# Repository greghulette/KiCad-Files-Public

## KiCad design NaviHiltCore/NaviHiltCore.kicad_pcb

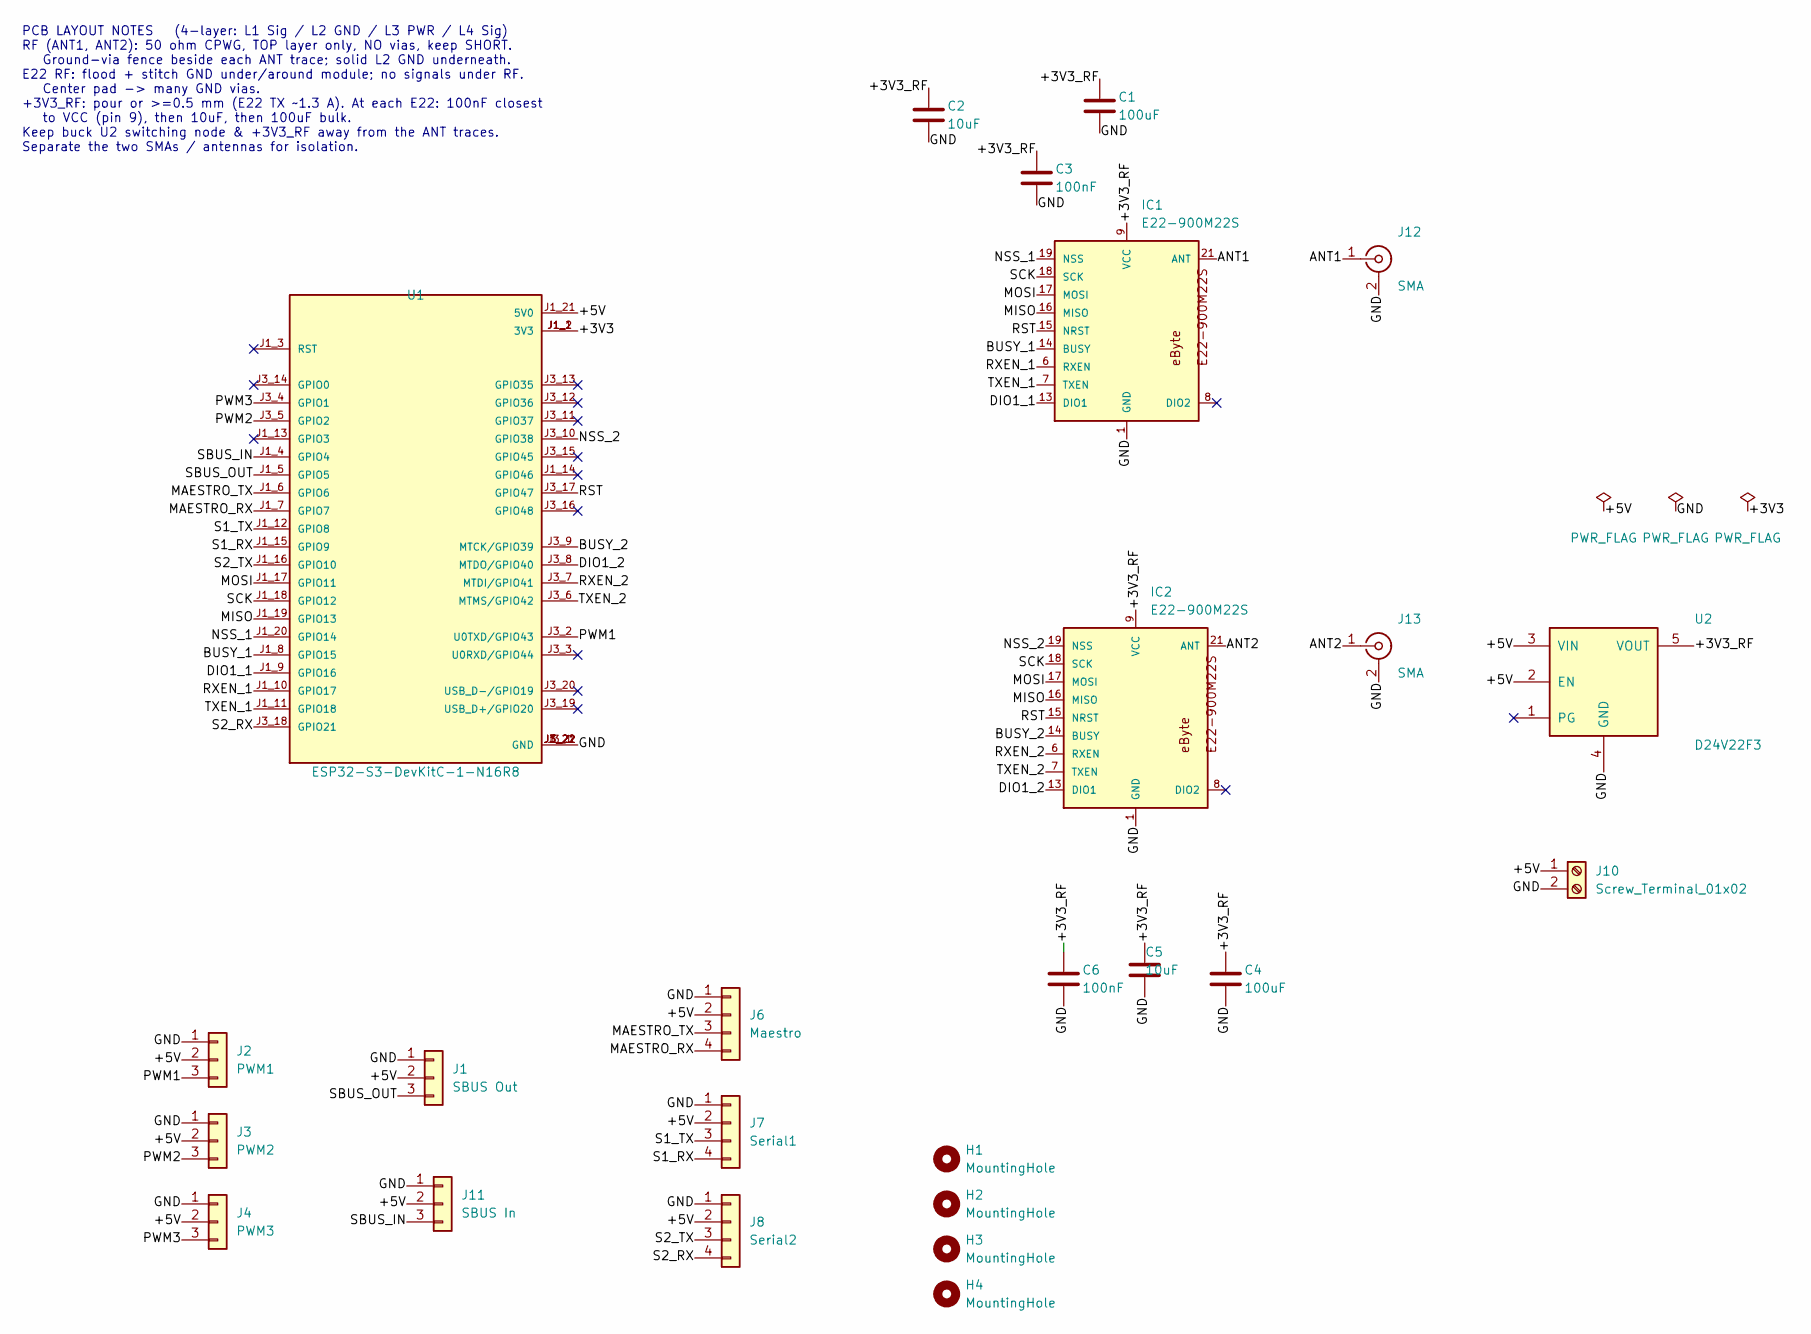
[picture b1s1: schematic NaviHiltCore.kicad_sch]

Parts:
C1, C4: 100uF; C_0805_2012Metric
C2, C5: 10uF; C_0805_2012Metric
C3, C6: 100nF; C_0805_2012Metric
H1, H2, H3, H4: MountingHole; MountingHole_3.2mm_M3
IC1, IC2: E22-900M22S
J1: SBUS Out; PinHeader_1x03_P2.54mm_Vertical
J2: PWM1; PinHeader_1x03_P2.54mm_Vertical
J3: PWM2; PinHeader_1x03_P2.54mm_Vertical
J4: PWM3; PinHeader_1x03_P2.54mm_Vertical
J6: Maestro; PinHeader_1x04_P2.54mm_Vertical
J7: Serial1; PinHeader_1x04_P2.54mm_Vertical
J8: Serial2; PinHeader_1x04_P2.54mm_Vertical
J10: Screw_Terminal_01x02; TerminalBlock_CUI_TB007-508-02_1x02_P5.08mm_Horizontal
J11: SBUS In; PinHeader_1x03_P2.54mm_Vertical
J12, J13: SMA; SMA_Amphenol_132134_Vertical
U1: ESP32-S3-DevKitC-1-N16R8; ESP32-S3DevKit-Multi
U2: D24V22F3

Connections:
/+3V3: U1.J1_1 (3V3), U1.J1_2 (3V3)
/+3V3_RF: C1.1, C2.1, C3.1, C4.1, C5.1, C6.1, IC1.9 (VCC), IC2.9 (VCC), U2.5 (VOUT)
/+5V: J1.2, J2.2, J3.2, J4.2, J6.2, J7.2, J8.2, J10.1, J11.2, U1.J1_21 (5V0), U2.2 (EN), U2.3 (VIN)
/ANT1: IC1.21 (ANT), J12.1 (In)
/ANT2: IC2.21 (ANT), J13.1 (In)
/BUSY_1: IC1.14 (BUSY), U1.J1_8 (GPIO15)
/BUSY_2: IC2.14 (BUSY), U1.J3_9 (MTCK/GPIO39)
/DIO1_1: IC1.13 (DIO1), U1.J1_9 (GPIO16)
/DIO1_2: IC2.13 (DIO1), U1.J3_8 (MTDO/GPIO40)
/MAESTRO_RX: J6.4, U1.J1_7 (GPIO7)
/MAESTRO_TX: J6.3, U1.J1_6 (GPIO6)
/MISO: IC1.16 (MISO), IC2.16 (MISO), U1.J1_19 (GPIO13)
/MOSI: IC1.17 (MOSI), IC2.17 (MOSI), U1.J1_17 (GPIO11)
/NSS_1: IC1.19 (NSS), U1.J1_20 (GPIO14)
/NSS_2: IC2.19 (NSS), U1.J3_10 (GPIO38)
/PWM1: J2.3, U1.J3_2 (U0TXD/GPIO43)
/PWM2: J3.3, U1.J3_5 (GPIO2)
/PWM3: J4.3, U1.J3_4 (GPIO1)
/RST: IC1.15 (NRST), IC2.15 (NRST), U1.J3_17 (GPIO47)
/RXEN_1: IC1.6 (RXEN), U1.J1_10 (GPIO17)
/RXEN_2: IC2.6 (RXEN), U1.J3_7 (MTDI/GPIO41)
/S1_RX: J7.4, U1.J1_15 (GPIO9)
/S1_TX: J7.3, U1.J1_12 (GPIO8)
/S2_RX: J8.4, U1.J3_18 (GPIO21)
/S2_TX: J8.3, U1.J1_16 (GPIO10)
/SBUS_IN: J11.3, U1.J1_4 (GPIO4)
/SBUS_OUT: J1.3, U1.J1_5 (GPIO5)
/SCK: IC1.18 (SCK), IC2.18 (SCK), U1.J1_18 (GPIO12)
/TXEN_1: IC1.7 (TXEN), U1.J1_11 (GPIO18)
/TXEN_2: IC2.7 (TXEN), U1.J3_6 (MTMS/GPIO42)
GND: C1.2, C2.2, C3.2, C4.2, C5.2, C6.2, IC1.1 (GND), IC1.2 (GND), IC1.3 (GND), IC1.4 (GND), IC1.5 (GND), IC1.10 (GND), IC1.11 (GND), IC1.12 (GND), IC1.20 (GND), IC1.22 (GND), IC2.1 (GND), IC2.2 (GND), IC2.3 (GND), IC2.4 (GND), IC2.5 (GND), IC2.10 (GND), IC2.11 (GND), IC2.12 (GND), IC2.20 (GND), IC2.22 (GND), J1.1, J2.1, J3.1, J4.1, J6.1, J7.1, J8.1, J10.2, J11.1, J12.2 (Ext), J13.2 (Ext), U1.J1_22 (GND), U1.J3_1 (GND), U1.J3_21 (GND), U1.J3_22 (GND), U2.4 (GND)

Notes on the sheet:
PCB LAYOUT NOTES (4-layer: L1 Sig / L2 GND / L3 PWR / L4 Sig) RF (ANT1, ANT2): 50 ohm CPWG, TOP layer only, NO vias, keep SHORT. Ground-via fence beside each ANT trace; solid L2 GND underneath. E22 RF: flood + stitch GND under/around module; no signals under RF. Center pad -> many GND vias. +3V3_RF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

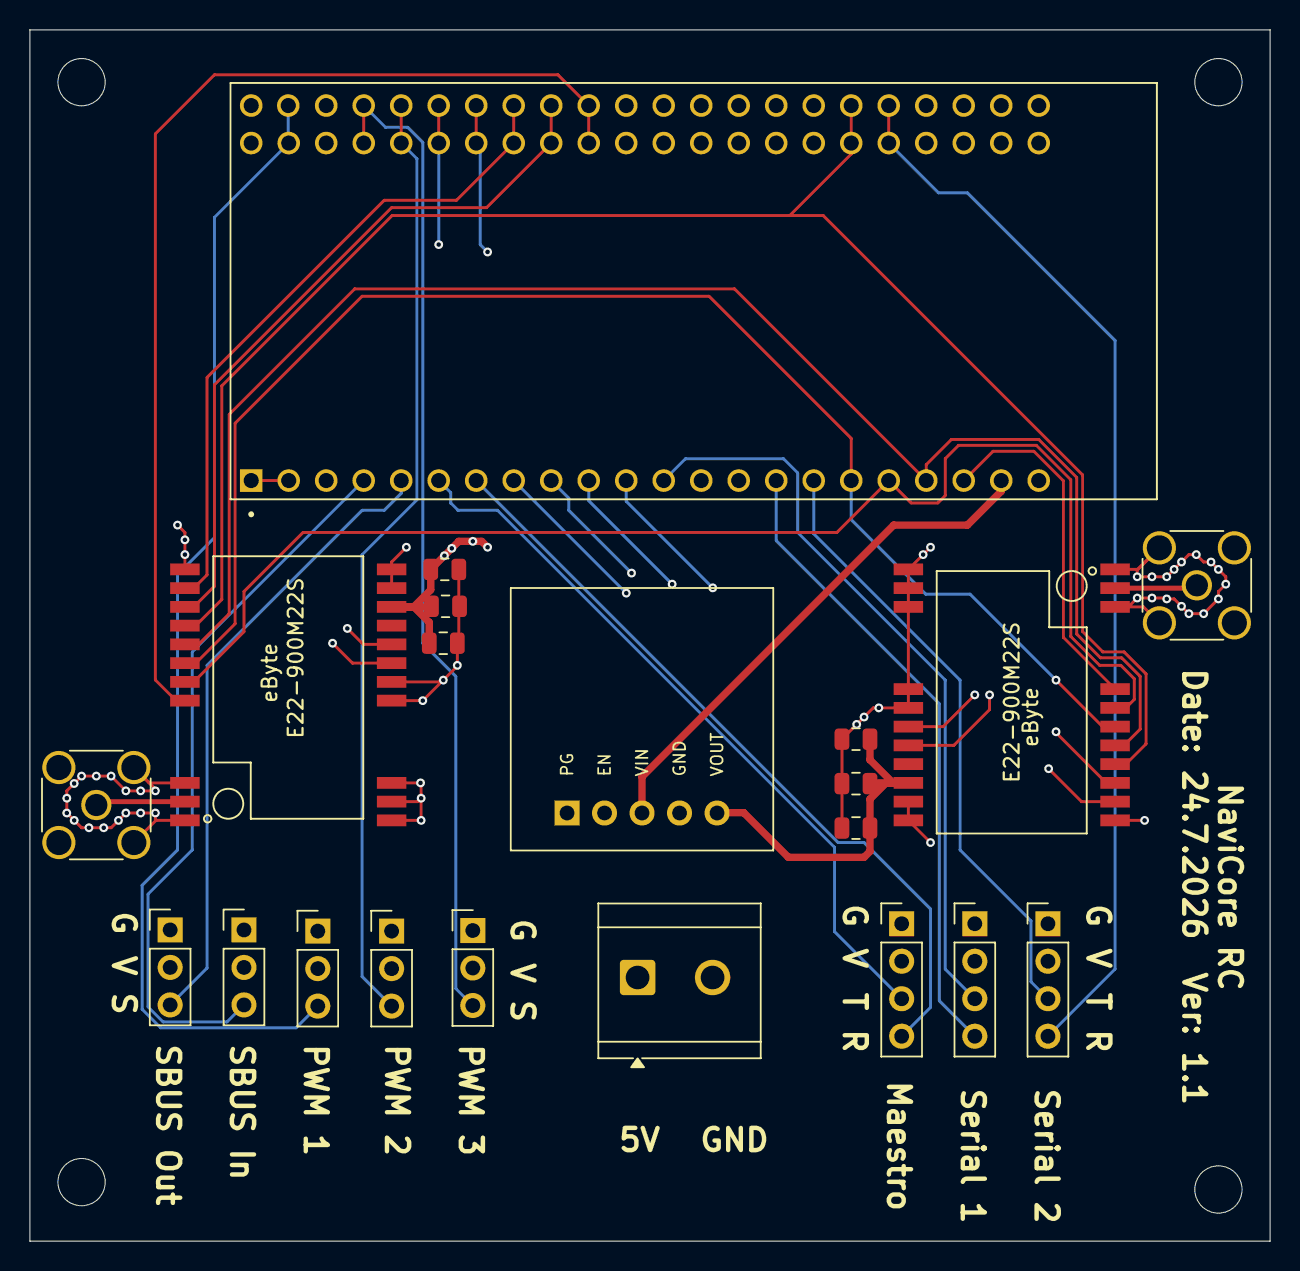
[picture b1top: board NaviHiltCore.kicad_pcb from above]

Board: 4 copper layers, 84.0 x 82.0 mm, 25 parts (0 on the bottom side), 31 nets.

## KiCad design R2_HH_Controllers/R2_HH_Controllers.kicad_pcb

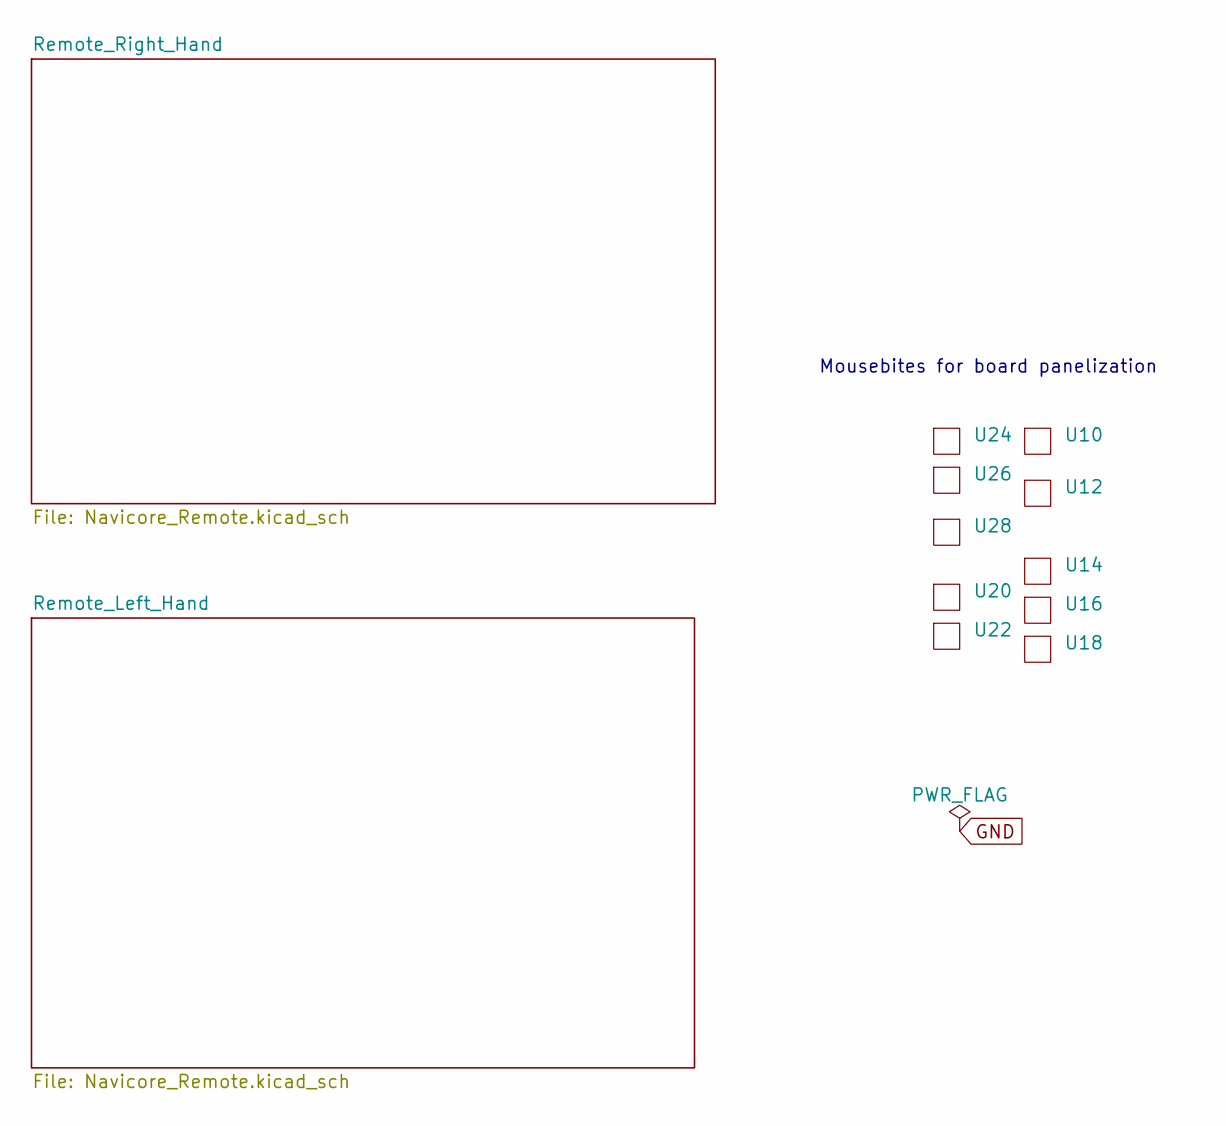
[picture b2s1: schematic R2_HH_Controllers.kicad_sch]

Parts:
U10, U12, U14, U16, U18, U20, U22, U24, U26, U28: mouse-bite-2.54mm-slot

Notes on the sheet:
Mousebites for board panelization

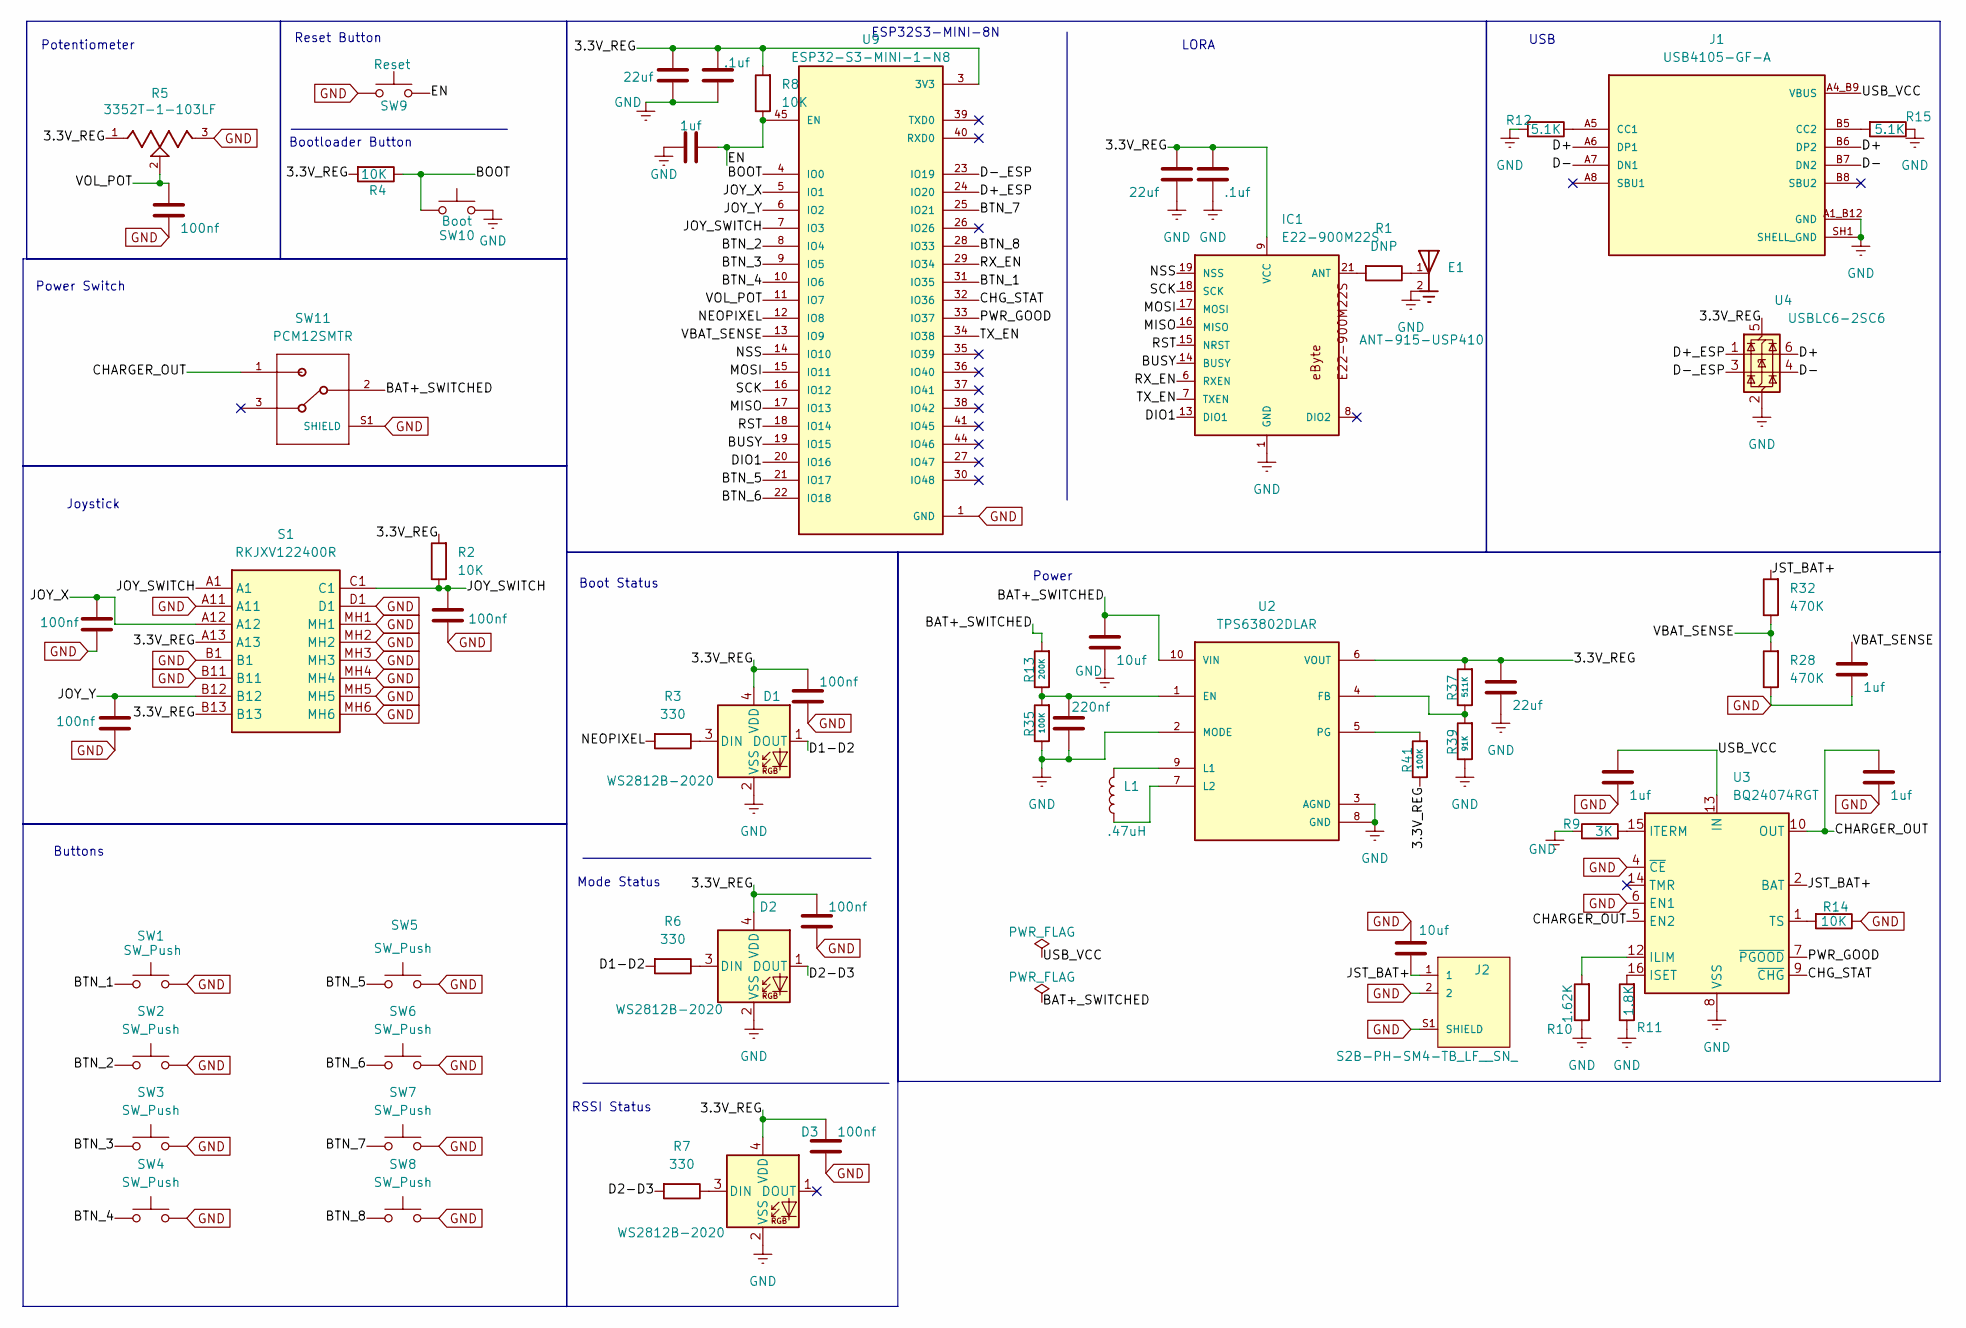
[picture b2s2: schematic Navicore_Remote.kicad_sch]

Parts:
C1, C3, C5, C6, C7, C12, C14: 100nf; C_0603_1608Metric
C2: 22uf; C_0805_2012Metric_Pad1.18x1.45mm_HandSolder
C4: .1uf; C_0805_2012Metric_Pad1.18x1.45mm_HandSolder
C8, C40: 22uf; C_0603_1608Metric
C9: .1uf; C_0603_1608Metric
C10, C16, C17: 1uf; C_0603_1608Metric
C18, C42: 10uf; C_0603_1608Metric
C33: 220nf; C_0603_1608Metric
C37: 1uf; C_0805_2012Metric_Pad1.18x1.45mm_HandSolder
D1, D2, D3: WS2812B-2020; LED_WS2812B-2020_PLCC4_2.0x2.0mm
E1: ANT-915-USP410; XDCR_ANT-915-USP410; PARTREV N/A
IC1: E22-900M22S
J1: USB4105-GF-A; GCT_USB4105-GF-A; PARTREV B4
J2: S2B-PH-SM4-TB_LF__SN_; JST_S2B-PH-SM4-TB_LF__SN_
L1: .47uH; L_0603_1608Metric
R1: DNP; R_0805_2012Metric_Pad1.20x1.40mm_HandSolder
R2, R4, R8, R14: 10K; R_0603_1608Metric
R3, R6, R7: 330; R_0603_1608Metric
R5: 3352T-1-103LF; TRIM_3352T-1-103LF; PARTREV 08/19
R9: 3K; R_0603_1608Metric
R10: 1.62K; R_0603_1608Metric
R11: 1.8K; R_0603_1608Metric
R12, R15: 5.1K; R_0603_1608Metric
R13: 200K; R_0603_1608Metric
R28, R32: 470K; R_0805_2012Metric_Pad1.20x1.40mm_HandSolder
R35, R41: 100K; R_0603_1608Metric
R37: 511K; R_0603_1608Metric
R39: 91K; R_0603_1608Metric
S1: RKJXV122400R; Manufacturer_Part_Number RKJXV122400R; Mouser Part Number 688-RKJXV122400R
SW1, SW2, SW3, SW4, SW5, SW6, SW7, SW8: SW_Push; SW_TL3360AF185Q
SW9: Reset; SW_SPST_TL3342
SW10: Boot; SW_SPST_TL3342
SW11: PCM12SMTR; SW_PCM12SMTR
U2: TPS63802DLAR; VREG_TPS63802DLAR; PARTREV B
U3: BQ24074RGT; VQFN-16-1EP_3x3mm_P0.5mm_EP1.6x1.6mm
U4: USBLC6-2SC6; SOT-23-6
U9: ESP32-S3-MINI-1-N8; XCVR_ESP32-S3-MINI-1-N8; PARTREV v0.6

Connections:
/Remote_Right_Hand/3.3V_REG: C2.2, C4.2, C7.2, C8.2, C9.2, C12.2, C14.2, C40.2, D1.4 (VDD), D2.4 (VDD), D3.4 (VDD), IC1.9 (VCC), R2.2, R4.2, R5.1, R8.2, R37.2, R41.1, S1.A13, S1.B13, U2.6 (VOUT), U4.5 (VBUS), U9.3 (3V3)
/Remote_Right_Hand/BAT+_SWITCHED: C42.2, R13.2, SW11.2, U2.10 (VIN)
/Remote_Right_Hand/BOOT: R4.1, SW10.1, U9.4 (IO0)
/Remote_Right_Hand/BTN_1: SW1.1, U9.31 (IO35)
/Remote_Right_Hand/BTN_2: SW2.1, U9.8 (IO4)
/Remote_Right_Hand/BTN_3: SW3.1, U9.9 (IO5)
/Remote_Right_Hand/BTN_4: SW4.1, U9.10 (IO6)
/Remote_Right_Hand/BTN_5: SW5.1, U9.21 (IO17)
/Remote_Right_Hand/BTN_6: SW6.1, U9.22 (IO18)
/Remote_Right_Hand/BTN_7: SW7.1, U9.25 (IO21)
/Remote_Right_Hand/BTN_8: SW8.1, U9.28 (IO33)
/Remote_Right_Hand/BUSY: IC1.14 (BUSY), U9.19 (IO15)
/Remote_Right_Hand/CHARGER_OUT: C17.2, SW11.1, U3.5 (EN2), U3.10 (OUT), U3.11 (OUT)
/Remote_Right_Hand/CHG_STAT: U3.9 (~CHG), U9.32 (IO36)
/Remote_Right_Hand/D1-D2: D1.1 (DOUT), R6.2
/Remote_Right_Hand/D2-D3: D2.1 (DOUT), R7.2
/Remote_Right_Hand/D+: J1.A6 (DP1), J1.B6 (DP2), U4.6 (I/O1)
/Remote_Right_Hand/D+_ESP: U4.1 (I/O1), U9.24 (IO20)
/Remote_Right_Hand/D-: J1.A7 (DN1), J1.B7 (DN2), U4.4 (I/O2)
/Remote_Right_Hand/D-_ESP: U4.3 (I/O2), U9.23 (IO19)
/Remote_Right_Hand/DIO1: IC1.13 (DIO1), U9.20 (IO16)
/Remote_Right_Hand/EN: C10.2, R8.1, SW9.2, U9.45 (EN)
/Remote_Right_Hand/JOY_SWITCH: C5.2, R2.1, S1.A1, S1.C1, U9.7 (IO3)
/Remote_Right_Hand/JOY_X: C1.2, S1.A12, U9.5 (IO1)
/Remote_Right_Hand/JOY_Y: C3.2, S1.B12, U9.6 (IO2)
/Remote_Right_Hand/JST_BAT+: C18.1, J2.1, R32.2, U3.2 (BAT), U3.3 (BAT)
/Remote_Right_Hand/MISO: IC1.16 (MISO), U9.17 (IO13)
/Remote_Right_Hand/MOSI: IC1.17 (MOSI), U9.15 (IO11)
/Remote_Right_Hand/NEOPIXEL: R3.2, U9.12 (IO8)
/Remote_Right_Hand/NSS: IC1.19 (NSS), U9.14 (IO10)
/Remote_Right_Hand/PWR_GOOD: U3.7 (~PGOOD), U9.33 (IO37)
/Remote_Right_Hand/RST: IC1.15 (NRST), U9.18 (IO14)
/Remote_Right_Hand/RX_EN: IC1.6 (RXEN), U9.29 (IO34)
/Remote_Right_Hand/SCK: IC1.18 (SCK), U9.16 (IO12)
/Remote_Right_Hand/TX_EN: IC1.7 (TXEN), U9.34 (IO38)
/Remote_Right_Hand/VBAT_SENSE: C37.2, R28.2, R32.1, U9.13 (IO9)
/Remote_Right_Hand/VOL_POT: C6.2, R5.2, U9.11 (IO7)
GND: C1.1, C2.1, C3.1, C4.1, C5.1, C6.1, C7.1, C8.1, C9.1, C10.1, C12.1, C14.1, C16.1, C17.1, C18.2, C33.1, C37.1, C40.1, C42.1, D1.2 (VSS), D2.2 (VSS), D3.2 (VSS), E1.2, IC1.1 (GND), IC1.2 (GND), IC1.3 (GND), IC1.4 (GND), IC1.5 (GND), IC1.10 (GND), IC1.11 (GND), IC1.12 (GND), IC1.20 (GND), IC1.22 (GND), J1.A1_B12 (GND), J1.B1_A12 (GND), J1.SH1 (SHELL_GND), J1.SH2 (SHELL_GND), J1.SH3 (SHELL_GND), J1.SH4 (SHELL_GND), J2.2, J2.S1 (SHIELD), J2.S2 (SHIELD), R5.3, R9.1, R10.1, R11.1, R12.2, R14.1, R15.1, R28.1, R35.1, R39.1, S1.A11, S1.B1, S1.B11, S1.D1, S1.MH1, S1.MH2, S1.MH3, S1.MH4, S1.MH5, S1.MH6, SW1.2, SW2.2, SW3.2, SW4.2, SW5.2, SW6.2, SW7.2, SW8.2, SW9.1, SW10.2, SW11.S1 (SHIELD), SW11.S2 (SHIELD), SW11.S3 (SHIELD), SW11.S4 (SHIELD), U2.2 (MODE), U2.3 (AGND), U2.8 (GND), U3.4 (~CE), U3.6 (EN1), U3.8 (VSS), U3.17 (VSS), U4.2 (GND), U9.1 (GND), U9.2 (GND), U9.42 (GND), U9.43 (GND), U9.46 (GND), U9.47 (GND), U9.48 (GND), U9.49 (GND), U9.50 (GND), U9.51 (GND), U9.52 (GND), U9.53 (GND), U9.54 (GND), U9.55 (GND), U9.56 (GND), U9.57 (GND), U9.58 (GND), U9.59 (GND), U9.60 (GND), U9.61 (GND), U9.61_1 (GND), U9.61_2 (GND), U9.61_3 (GND), U9.61_4 (GND), U9.61_5 (GND), U9.61_6 (GND), U9.61_7 (GND), U9.61_8 (GND), U9.62 (GND), U9.63 (GND), U9.64 (GND), U9.65 (GND); also elsewhere on the board
unnamed: D1.3 (DIN), R3.1
unnamed: D2.3 (DIN), R6.1
unnamed: D3.3 (DIN), R7.1
unnamed: E1.1, R1.1
unnamed: IC1.21 (ANT), R1.2
unnamed: J1.A5 (CC1), R12.1
unnamed: J1.B5 (CC2), R15.2
unnamed: C33.2, R13.1, R35.2, U2.1 (EN)
unnamed: R37.1, R39.2, U2.4 (FB)
unnamed: L1.2, U2.9 (L1)
unnamed: L1.1, U2.7 (L2)
unnamed: R41.2, U2.5 (PG)
unnamed: R10.2, U3.12 (ILIM)
unnamed: R11.2, U3.16 (ISET)
unnamed: R9.2, U3.15 (ITERM)
unnamed: R14.2, U3.1 (TS)
VBUS: C16.2, J1.A4_B9 (VBUS), J1.B4_A9 (VBUS), U3.13 (IN); also elsewhere on the board

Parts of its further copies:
C19, C21, C23, C24, C25, C30, C32: 100nf; C_0603_1608Metric
C20: 22uf; C_0805_2012Metric_Pad1.18x1.45mm_HandSolder
C22: .1uf; C_0805_2012Metric_Pad1.18x1.45mm_HandSolder
C26, C41: 22uf; C_0603_1608Metric
C27: .1uf; C_0603_1608Metric
C28, C34, C35: 1uf; C_0603_1608Metric
C36, C43: 10uf; C_0603_1608Metric
C38: 1uf; C_0805_2012Metric_Pad1.18x1.45mm_HandSolder
C39: 220nf; C_0603_1608Metric
D4, D5, D6: WS2812B-2020; LED_WS2812B-2020_PLCC4_2.0x2.0mm
E2: ANT-915-USP410; XDCR_ANT-915-USP410; PARTREV N/A
IC2: E22-900M22S
J3: USB4105-GF-A; GCT_USB4105-GF-A; PARTREV B4
J4: S2B-PH-SM4-TB_LF__SN_; JST_S2B-PH-SM4-TB_LF__SN_
L2: .47uH; L_0603_1608Metric
R16: DNP; R_0805_2012Metric_Pad1.20x1.40mm_HandSolder
R17, R19, R23, R29: 10K; R_0603_1608Metric
R18, R21, R22: 330; R_0603_1608Metric
R20: 3352T-1-103LF; TRIM_3352T-1-103LF; PARTREV 08/19
R24: 3K; R_0603_1608Metric
R25: 1.62K; R_0603_1608Metric
R26: 1.8K; R_0603_1608Metric
R27, R30: 5.1K; R_0603_1608Metric
R31, R33: 470K; R_0805_2012Metric_Pad1.20x1.40mm_HandSolder
R34: 200K; R_0603_1608Metric
R36, R42: 100K; R_0603_1608Metric
R38: 511K; R_0603_1608Metric
R40: 91K; R_0603_1608Metric
S2: RKJXV122400R; Manufacturer_Part_Number RKJXV122400R; Mouser Part Number 688-RKJXV122400R
SW12, SW13, SW14, SW15, SW16, SW17, SW18, SW19: SW_Push; SW_TL3360AF185Q
SW20: Reset; SW_SPST_TL3342
SW21: Boot; SW_SPST_TL3342
SW22: PCM12SMTR; SW_PCM12SMTR
U6: TPS63802DLAR; VREG_TPS63802DLAR; PARTREV B
U7: BQ24074RGT; VQFN-16-1EP_3x3mm_P0.5mm_EP1.6x1.6mm
U8: USBLC6-2SC6; SOT-23-6
U11: ESP32-S3-MINI-1-N8; XCVR_ESP32-S3-MINI-1-N8; PARTREV v0.6

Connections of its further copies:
/Remote_Left_Hand/3.3V_REG: C20.2, C22.2, C25.2, C26.2, C27.2, C30.2, C32.2, C41.2, D4.4 (VDD), D5.4 (VDD), D6.4 (VDD), IC2.9 (VCC), R17.2, R19.2, R20.1, R23.2, R38.2, R42.1, S2.A13, S2.B13, U6.6 (VOUT), U8.5 (VBUS), U11.3 (3V3)
/Remote_Left_Hand/BAT+_SWITCHED: C43.2, R34.2, SW22.2, U6.10 (VIN)
/Remote_Left_Hand/BOOT: R19.1, SW21.1, U11.4 (IO0)
/Remote_Left_Hand/BTN_1: SW12.1, U11.31 (IO35)
/Remote_Left_Hand/BTN_2: SW13.1, U11.8 (IO4)
/Remote_Left_Hand/BTN_3: SW14.1, U11.9 (IO5)
/Remote_Left_Hand/BTN_4: SW15.1, U11.10 (IO6)
/Remote_Left_Hand/BTN_5: SW16.1, U11.21 (IO17)
/Remote_Left_Hand/BTN_6: SW17.1, U11.22 (IO18)
/Remote_Left_Hand/BTN_7: SW18.1, U11.25 (IO21)
/Remote_Left_Hand/BTN_8: SW19.1, U11.28 (IO33)
/Remote_Left_Hand/BUSY: IC2.14 (BUSY), U11.19 (IO15)
/Remote_Left_Hand/CHARGER_OUT: C35.2, SW22.1, U7.5 (EN2), U7.10 (OUT), U7.11 (OUT)
/Remote_Left_Hand/CHG_STAT: U7.9 (~CHG), U11.32 (IO36)
/Remote_Left_Hand/D1-D2: D4.1 (DOUT), R21.2
/Remote_Left_Hand/D2-D3: D5.1 (DOUT), R22.2
/Remote_Left_Hand/D+: J3.A6 (DP1), J3.B6 (DP2), U8.6 (I/O1)
/Remote_Left_Hand/D+_ESP: U8.1 (I/O1), U11.24 (IO20)
/Remote_Left_Hand/D-: J3.A7 (DN1), J3.B7 (DN2), U8.4 (I/O2)
/Remote_Left_Hand/D-_ESP: U8.3 (I/O2), U11.23 (IO19)
/Remote_Left_Hand/DIO1: IC2.13 (DIO1), U11.20 (IO16)
/Remote_Left_Hand/EN: C28.2, R23.1, SW20.2, U11.45 (EN)
/Remote_Left_Hand/JOY_SWITCH: C23.2, R17.1, S2.A1, S2.C1, U11.7 (IO3)
/Remote_Left_Hand/JOY_X: C19.2, S2.A12, U11.5 (IO1)
/Remote_Left_Hand/JOY_Y: C21.2, S2.B12, U11.6 (IO2)
/Remote_Left_Hand/JST_BAT+: C36.1, J4.1, R33.2, U7.2 (BAT), U7.3 (BAT)
/Remote_Left_Hand/MISO: IC2.16 (MISO), U11.17 (IO13)
/Remote_Left_Hand/MOSI: IC2.17 (MOSI), U11.15 (IO11)
/Remote_Left_Hand/NEOPIXEL: R18.2, U11.12 (IO8)
/Remote_Left_Hand/NSS: IC2.19 (NSS), U11.14 (IO10)
/Remote_Left_Hand/PWR_GOOD: U7.7 (~PGOOD), U11.33 (IO37)
/Remote_Left_Hand/RST: IC2.15 (NRST), U11.18 (IO14)
/Remote_Left_Hand/RX_EN: IC2.6 (RXEN), U11.29 (IO34)
/Remote_Left_Hand/SCK: IC2.18 (SCK), U11.16 (IO12)
/Remote_Left_Hand/TX_EN: IC2.7 (TXEN), U11.34 (IO38)
/Remote_Left_Hand/VBAT_SENSE: C38.2, R31.2, R33.1, U11.13 (IO9)
/Remote_Left_Hand/VOL_POT: C24.2, R20.2, U11.11 (IO7)
GND: C19.1, C20.1, C21.1, C22.1, C23.1, C24.1, C25.1, C26.1, C27.1, C28.1, C30.1, C32.1, C34.1, C35.1, C36.2, C38.1, C39.1, C41.1, C43.1, D4.2 (VSS), D5.2 (VSS), D6.2 (VSS), E2.2, IC2.1 (GND), IC2.2 (GND), IC2.3 (GND), IC2.4 (GND), IC2.5 (GND), IC2.10 (GND), IC2.11 (GND), IC2.12 (GND), IC2.20 (GND), IC2.22 (GND), J3.A1_B12 (GND), J3.B1_A12 (GND), J3.SH1 (SHELL_GND), J3.SH2 (SHELL_GND), J3.SH3 (SHELL_GND), J3.SH4 (SHELL_GND), J4.2, J4.S1 (SHIELD), J4.S2 (SHIELD), R20.3, R24.1, R25.1, R26.1, R27.2, R29.1, R30.1, R31.1, R36.1, R40.1, S2.A11, S2.B1, S2.B11, S2.D1, S2.MH1, S2.MH2, S2.MH3, S2.MH4, S2.MH5, S2.MH6, SW12.2, SW13.2, SW14.2, SW15.2, SW16.2, SW17.2, SW18.2, SW19.2, SW20.1, SW21.2, SW22.S1 (SHIELD), SW22.S2 (SHIELD), SW22.S3 (SHIELD), SW22.S4 (SHIELD), U6.2 (MODE), U6.3 (AGND), U6.8 (GND), U7.4 (~CE), U7.6 (EN1), U7.8 (VSS), U7.17 (VSS), U8.2 (GND), U11.1 (GND), U11.2 (GND), U11.42 (GND), U11.43 (GND), U11.46 (GND), U11.47 (GND), U11.48 (GND), U11.49 (GND), U11.50 (GND), U11.51 (GND), U11.52 (GND), U11.53 (GND), U11.54 (GND), U11.55 (GND), U11.56 (GND), U11.57 (GND), U11.58 (GND), U11.59 (GND), U11.60 (GND), U11.61 (GND), U11.61_1 (GND), U11.61_2 (GND), U11.61_3 (GND), U11.61_4 (GND), U11.61_5 (GND), U11.61_6 (GND), U11.61_7 (GND), U11.61_8 (GND), U11.62 (GND), U11.63 (GND), U11.64 (GND), U11.65 (GND); also elsewhere on the board
unnamed: D4.3 (DIN), R18.1
unnamed: D5.3 (DIN), R21.1
unnamed: D6.3 (DIN), R22.1
unnamed: E2.1, R16.1
unnamed: IC2.21 (ANT), R16.2
unnamed: J3.A5 (CC1), R27.1
unnamed: J3.B5 (CC2), R30.2
unnamed: C39.2, R34.1, R36.2, U6.1 (EN)
unnamed: R38.1, R40.2, U6.4 (FB)
unnamed: L2.2, U6.9 (L1)
unnamed: L2.1, U6.7 (L2)
unnamed: R42.2, U6.5 (PG)
unnamed: R25.2, U7.12 (ILIM)
unnamed: R26.2, U7.16 (ISET)
unnamed: R24.2, U7.15 (ITERM)
unnamed: R29.2, U7.1 (TS)
VBUS: C34.2, J3.A4_B9 (VBUS), J3.B4_A9 (VBUS), U7.13 (IN); also elsewhere on the board

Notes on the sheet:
Buttons
ESP32S3-MINI-8N
Mode Status
USB
RSSI Status
Boot Status
LORA
Power
Bootloader Button
Joystick
Potentiometer
Power Switch
Reset Button

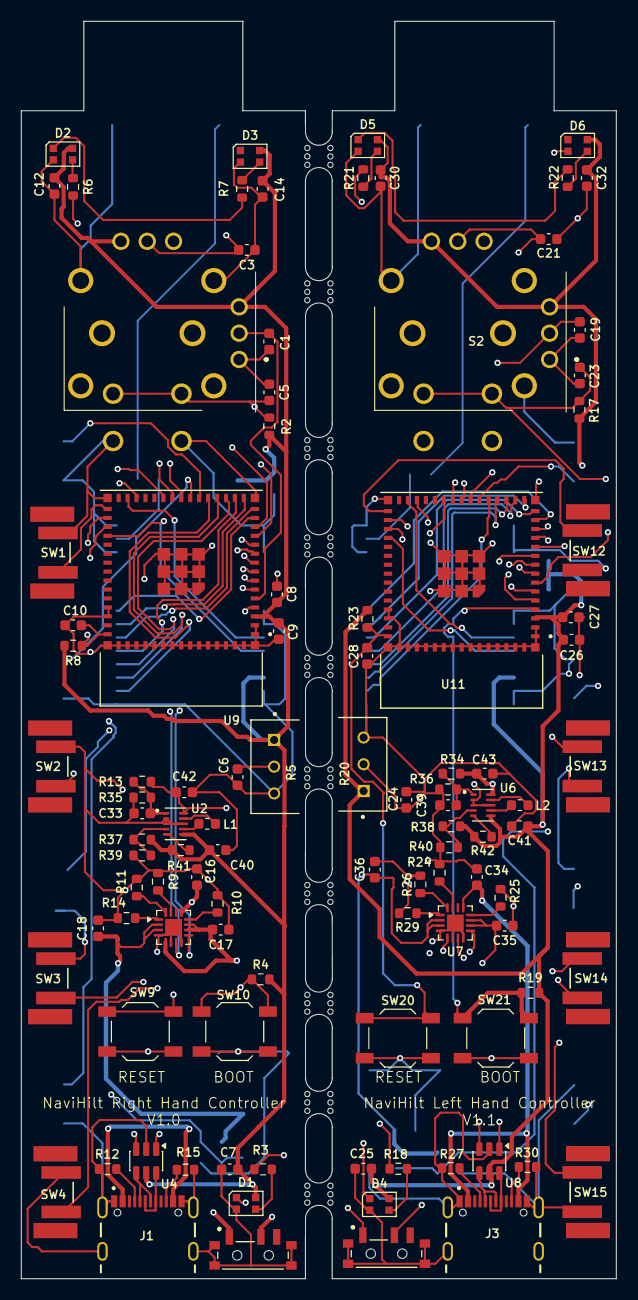
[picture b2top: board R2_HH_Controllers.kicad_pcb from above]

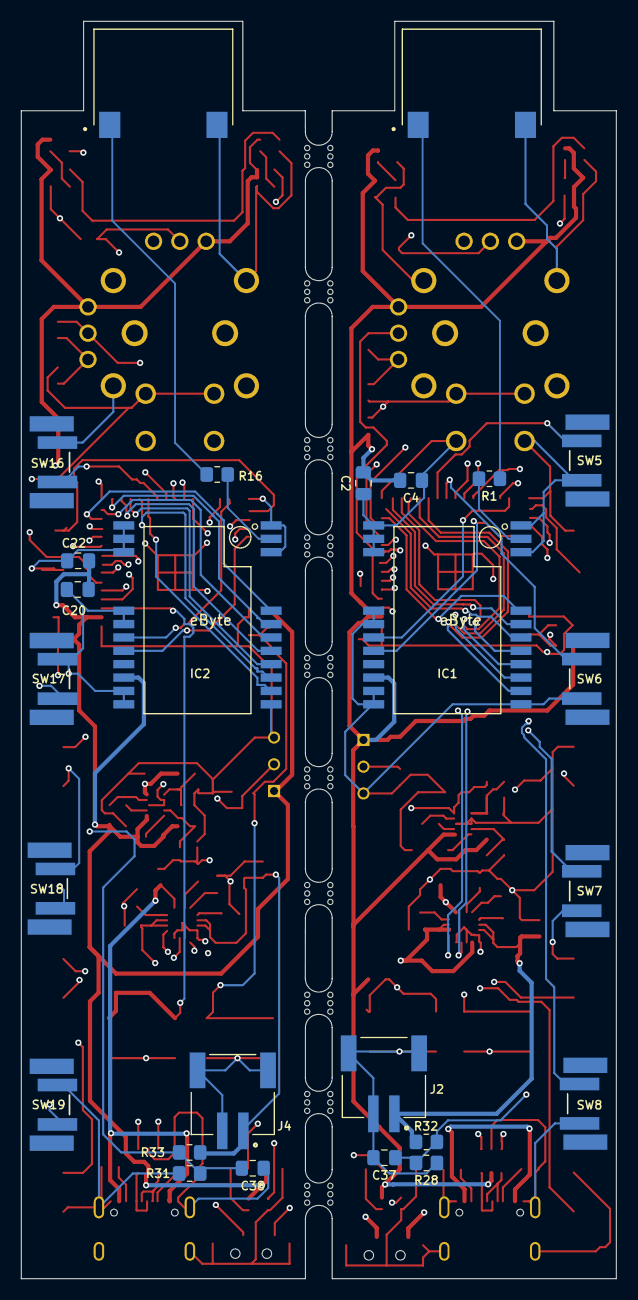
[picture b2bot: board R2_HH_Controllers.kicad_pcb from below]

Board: 4 copper layers, 56.5 x 119.5 mm, 138 parts (26 on the bottom side), 108 nets.

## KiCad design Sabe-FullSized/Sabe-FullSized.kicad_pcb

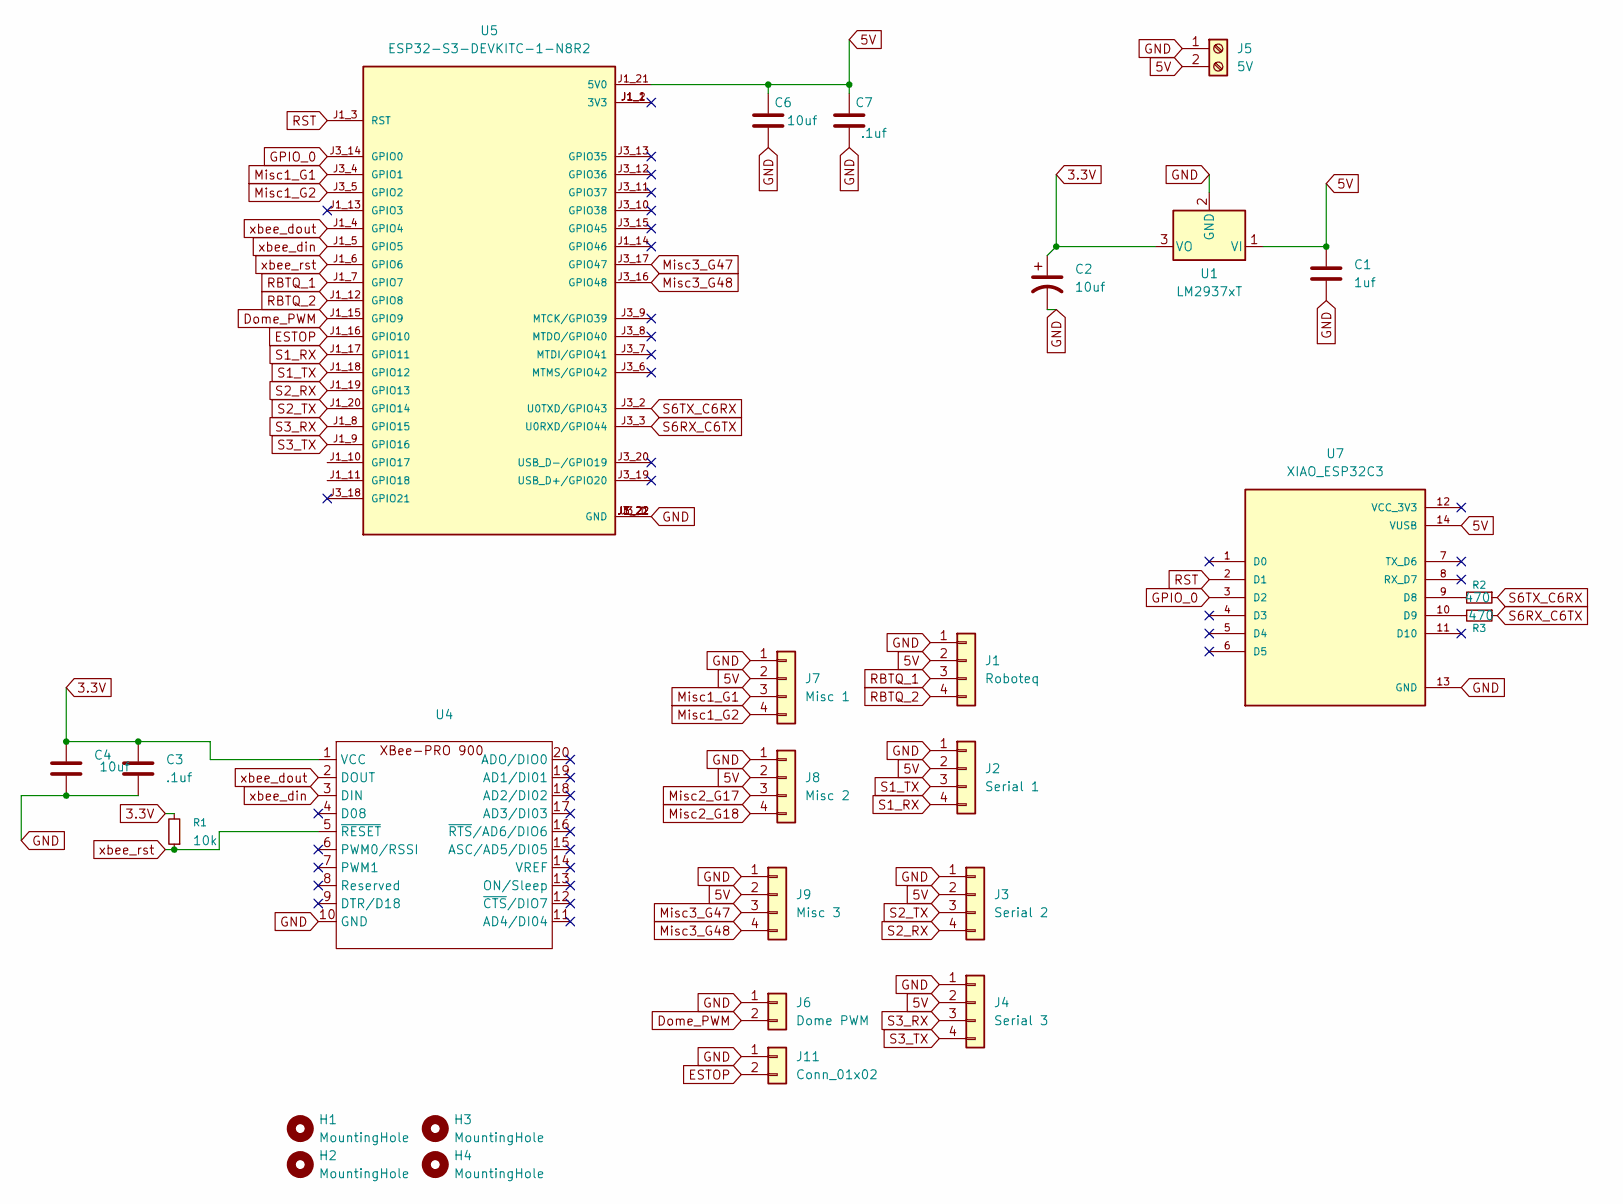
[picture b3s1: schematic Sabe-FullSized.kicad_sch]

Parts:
C1: 1uf; C_Disc_D7.5mm_W4.4mm_P5.00mm
C2, C4, C6: 10uf; CP_Radial_D5.0mm_P2.00mm
C3, C7: .1uf; C_Disc_D5.0mm_W2.5mm_P5.00mm
H1, H2, H3, H4: MountingHole; MountingHole_3.2mm_M3
J1: Roboteq; PinHeader_1x04_P2.54mm_Vertical
J2: Serial 1; PinHeader_1x04_P2.54mm_Vertical
J3: Serial 2; PinHeader_1x04_P2.54mm_Vertical
J4: Serial 3; PinHeader_1x04_P2.54mm_Vertical
J5: 5V; TerminalBlock_Phoenix_MKDS-1,5-2-5.08_1x02_P5.08mm_Horizont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
J6: Dome PWM; PinHeader_1x02_P2.54mm_Vertical
J7: Misc 1; PinHeader_1x04_P2.54mm_Vertical
J8: Misc 2; PinHeader_1x04_P2.54mm_Vertical
J9: Misc 3; PinHeader_1x04_P2.54mm_Vertical
J11: Conn_01x02; PinHeader_1x02_P2.54mm_Vertical
R1: 10k; R_Axial_DIN0207_L6.3mm_D2.5mm_P10.16mm_Horizontal
R2, R3: 470; R_Axial_DIN0207_L6.3mm_D2.5mm_P10.16mm_Horizontal
U1: LM2937xT; TO-220-3_Vertical
U4: XbeePro900
U5: ESP32-S3-DEVKITC-1-N8R2; XCVR_ESP32-S3-DEVKITC-1-N8R2; PARTREV V1
U7: XIAO_ESP32C3; MODULE_XIAO_ESP32C3; PARTREV 23/05/2022

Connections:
3.3V: C2.1, C3.1, C4.1, R1.2, U1.3 (VO), U4.1 (VCC)
5V: C1.1, C6.1, C7.1, J1.2, J2.2, J3.2, J4.2, J5.2, J7.2, J8.2, J9.2, U1.1 (VI), U5.J1_21 (5V0), U7.14 (VUSB)
Dome_PWM: J6.2, U5.J1_15 (GPIO9)
ESTOP: J11.2, U5.J1_16 (GPIO10)
GND: C1.2, C2.2, C3.2, C4.2, C6.2, C7.2, J1.1, J2.1, J3.1, J4.1, J5.1, J6.1, J7.1, J8.1, J9.1, J11.1, U1.2 (GND), U4.10 (GND), U5.J1_22 (GND), U5.J3_1 (GND), U5.J3_21 (GND), U5.J3_22 (GND), U7.13 (GND)
GPIO_0: U5.J3_14 (GPIO0), U7.3 (D2)
Misc1_G1: J7.3, U5.J3_4 (GPIO1)
Misc1_G2: J7.4, U5.J3_5 (GPIO2)
Misc2_G17: J8.3
Misc2_G18: J8.4
Misc3_G47: J9.3, U5.J3_17 (GPIO47)
Misc3_G48: J9.4, U5.J3_16 (GPIO48)
unnamed: R2.2, U7.9 (D8)
unnamed: R3.2, U7.10 (D9)
RBTQ_1: J1.3, U5.J1_7 (GPIO7)
RBTQ_2: J1.4, U5.J1_12 (GPIO8)
RST: U5.J1_3 (RST), U7.2 (D1)
S1_RX: J2.4, U5.J1_17 (GPIO11)
S1_TX: J2.3, U5.J1_18 (GPIO12)
S2_RX: J3.4, U5.J1_19 (GPIO13)
S2_TX: J3.3, U5.J1_20 (GPIO14)
S3_RX: J4.3, U5.J1_8 (GPIO15)
S3_TX: J4.4, U5.J1_9 (GPIO16)
S6RX_C6TX: R3.1, U5.J3_3 (U0RXD/GPIO44)
S6TX_C6RX: R2.1, U5.J3_2 (U0TXD/GPIO43)
xbee_din: U4.3 (DIN), U5.J1_5 (GPIO5)
xbee_dout: U4.2 (DOUT), U5.J1_4 (GPIO4)
xbee_rst: R1.1, U4.5 (~RESET), U5.J1_6 (GPIO6)

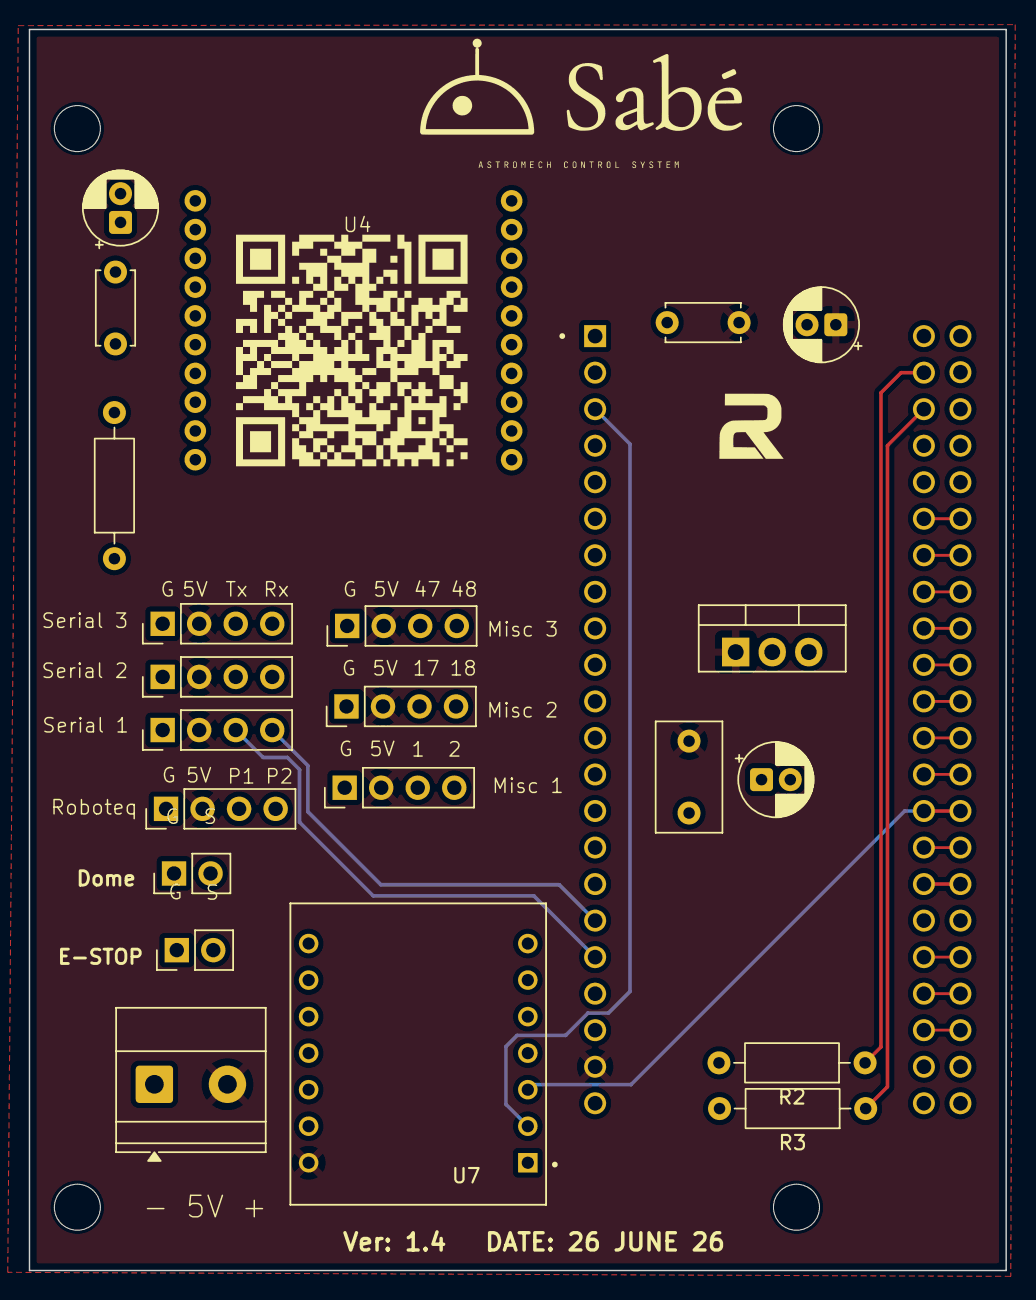
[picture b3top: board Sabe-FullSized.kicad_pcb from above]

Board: 4 copper layers, 67.9 x 86.3 mm, 27 parts (0 on the bottom side), 26 nets.
